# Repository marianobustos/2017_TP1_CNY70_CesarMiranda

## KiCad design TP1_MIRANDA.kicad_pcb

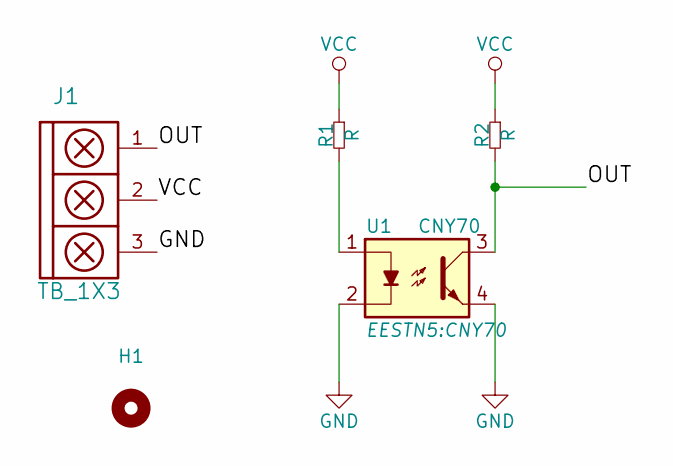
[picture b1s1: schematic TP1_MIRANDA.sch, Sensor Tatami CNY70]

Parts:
H1: Mounting_Hole; hole_3mm
J1: TB_1X3; Pin_Header_3
R1, R2: R; R_1206
U1: CNY70

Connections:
/OUT: J1.1, R2.2, U1.3
GND: J1.3, U1.2, U1.4
unnamed: R1.2, U1.1
VCC: J1.2, R1.1, R2.1

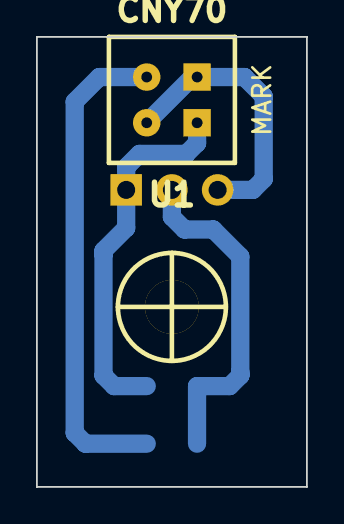
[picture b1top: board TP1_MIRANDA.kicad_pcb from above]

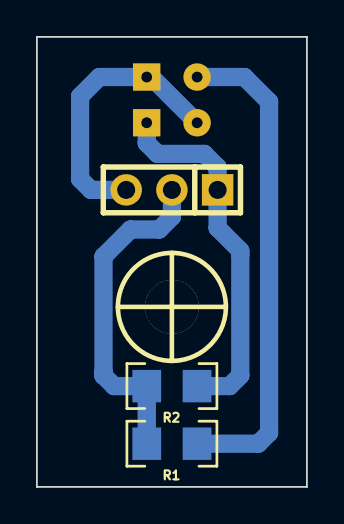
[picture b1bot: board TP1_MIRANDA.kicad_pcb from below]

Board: 2 copper layers, 15.0 x 25.0 mm, 5 parts (3 on the bottom side), 4 nets.

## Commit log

2018-03-25 Versión inicial
